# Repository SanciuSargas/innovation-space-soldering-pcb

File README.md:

# innovation-space-soldering-pcb
A beginner-friendly soldering practice PCB designed for workshops to teach fundamental soldering skills through a fun, hands-on project.

TODO: add soldering guide document

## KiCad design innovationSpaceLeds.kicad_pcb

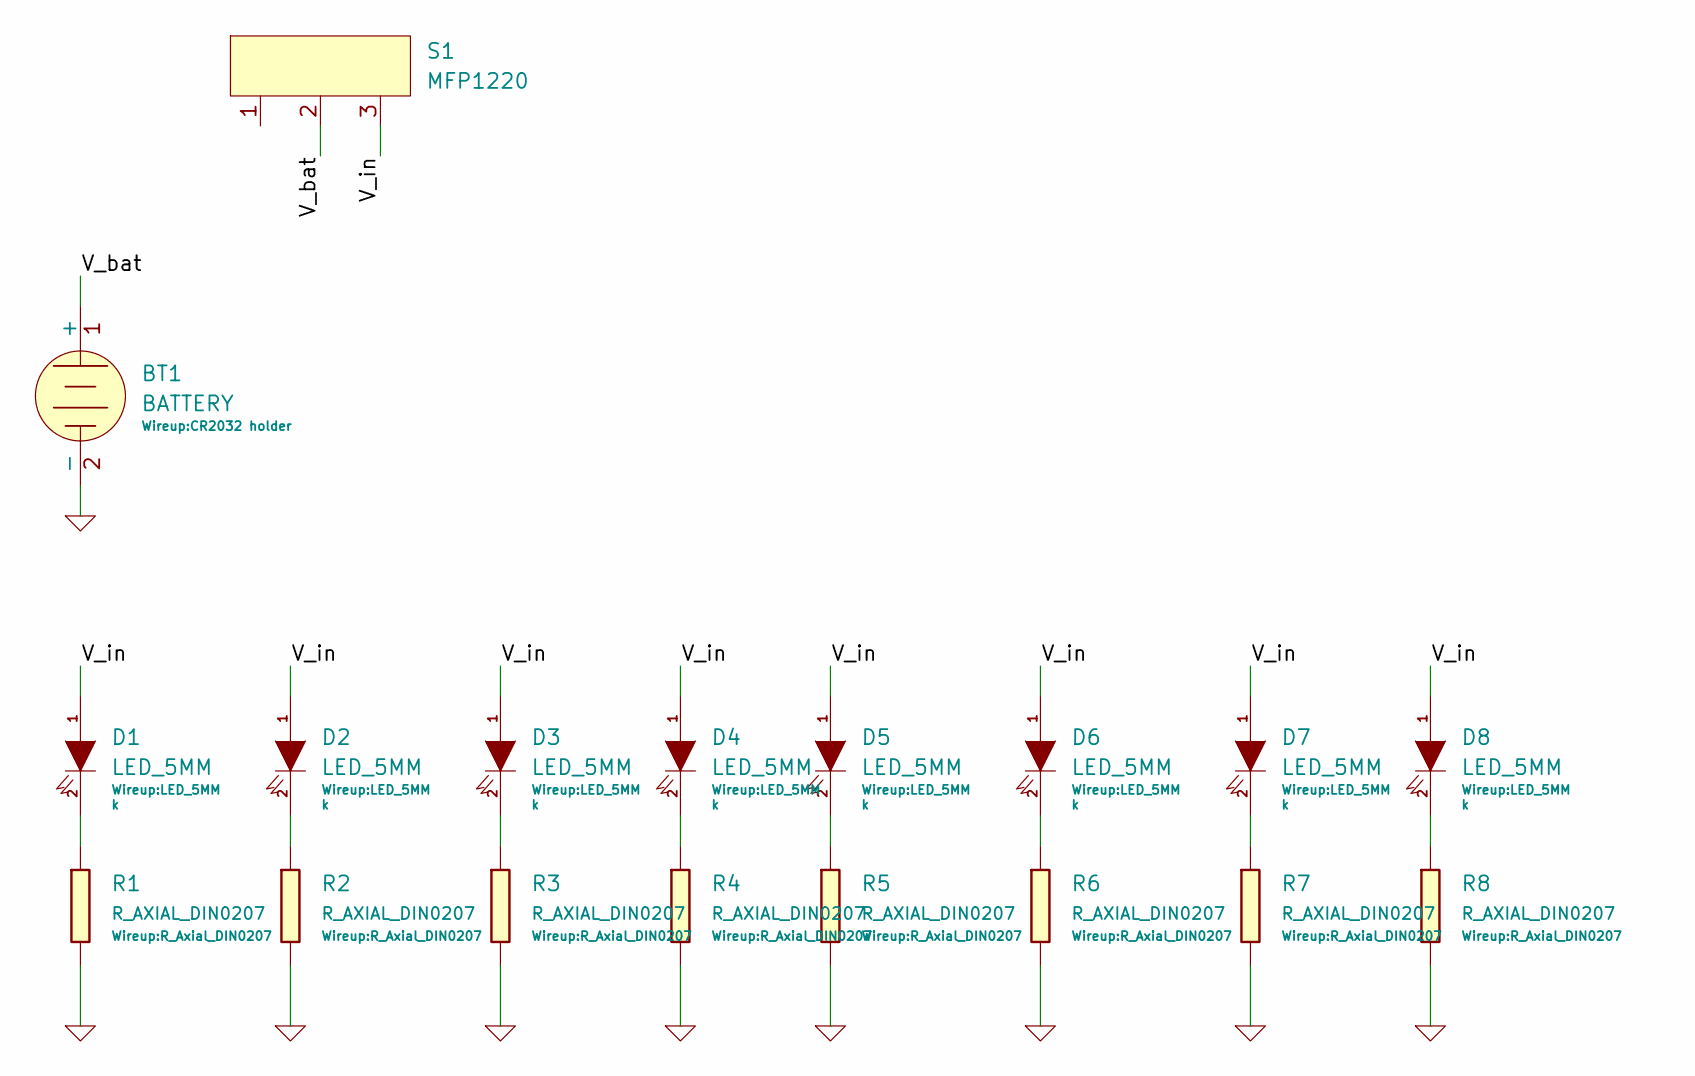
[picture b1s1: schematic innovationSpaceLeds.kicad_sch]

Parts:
BT1: BATTERY; CR2032 holder
D1, D2, D3, D4, D5, D6, D7, D8: LED_5MM
R1, R2, R3, R4, R5, R6, R7, R8: R_AXIAL_DIN0207; R_Axial_DIN0207
S1: MFP1220

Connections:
/V_bat: BT1.1 (+), S1.2
/V_in: D1.1 (A), D2.1 (A), D3.1 (A), D4.1 (A), D5.1 (A), D6.1 (A), D7.1 (A), D8.1 (A), S1.3
GND: BT1.2 (-), R1.2, R2.2, R3.2, R4.2, R5.2, R6.2, R7.2, R8.2
unnamed: D1.2 (K), R1.1
unnamed: D2.2 (K), R2.1
unnamed: D3.2 (K), R3.1
unnamed: D4.2 (K), R4.1
unnamed: D5.2 (K), R5.1
unnamed: D6.2 (K), R6.1
unnamed: D7.2 (K), R7.1
unnamed: D8.2 (K), R8.1

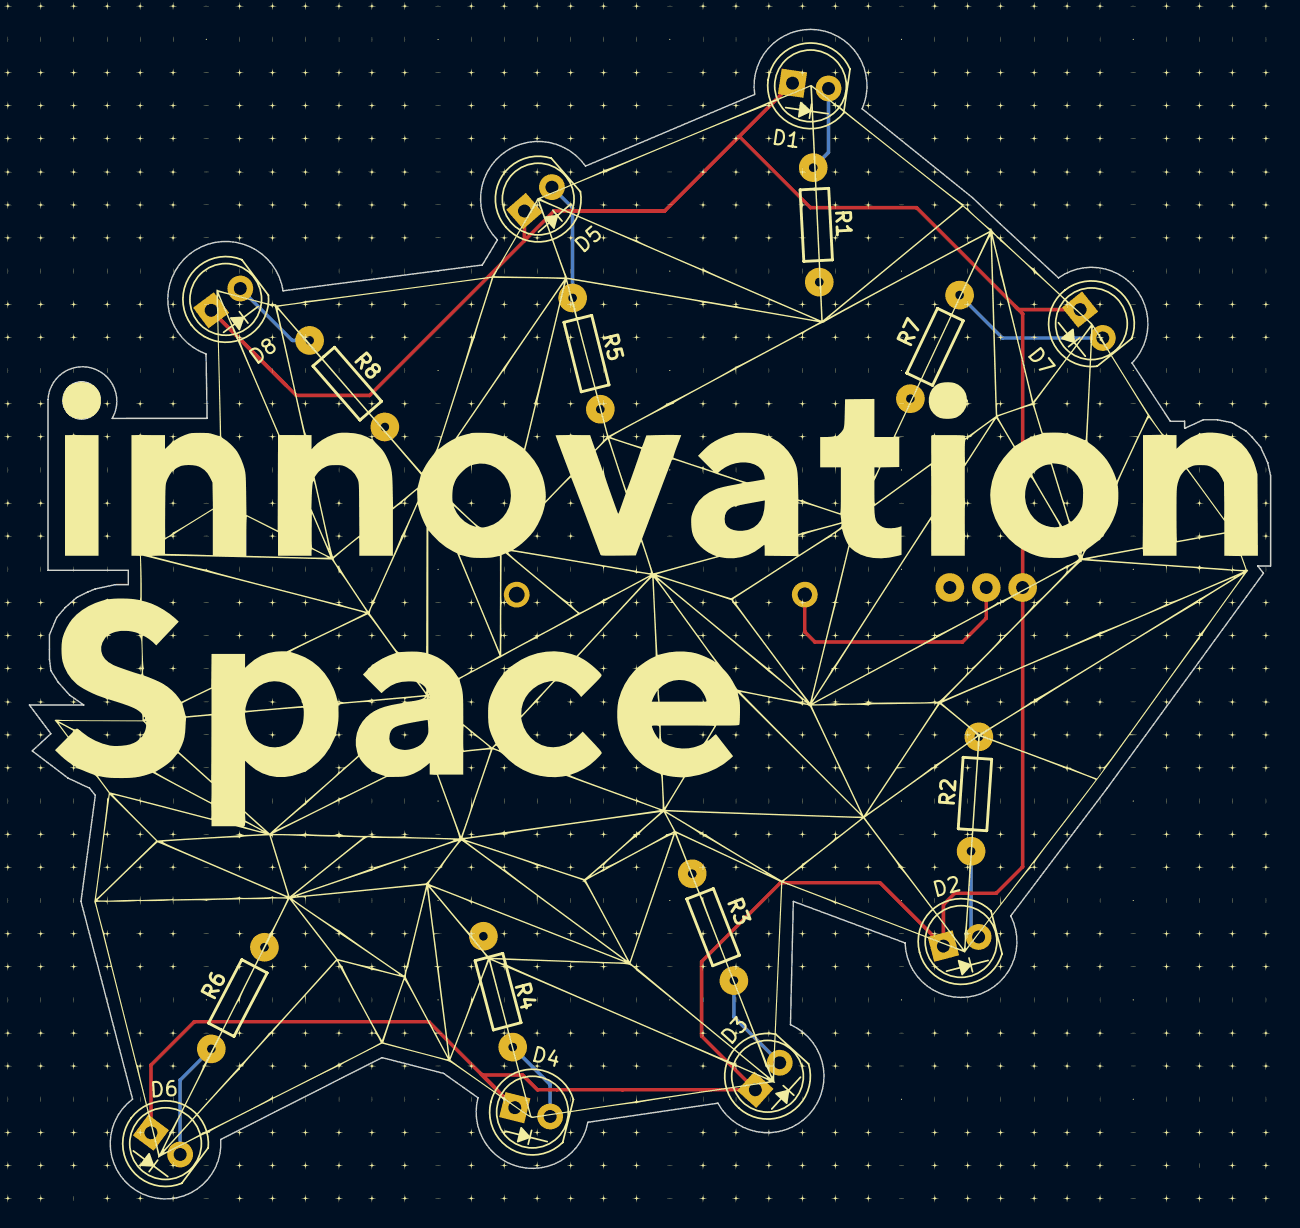
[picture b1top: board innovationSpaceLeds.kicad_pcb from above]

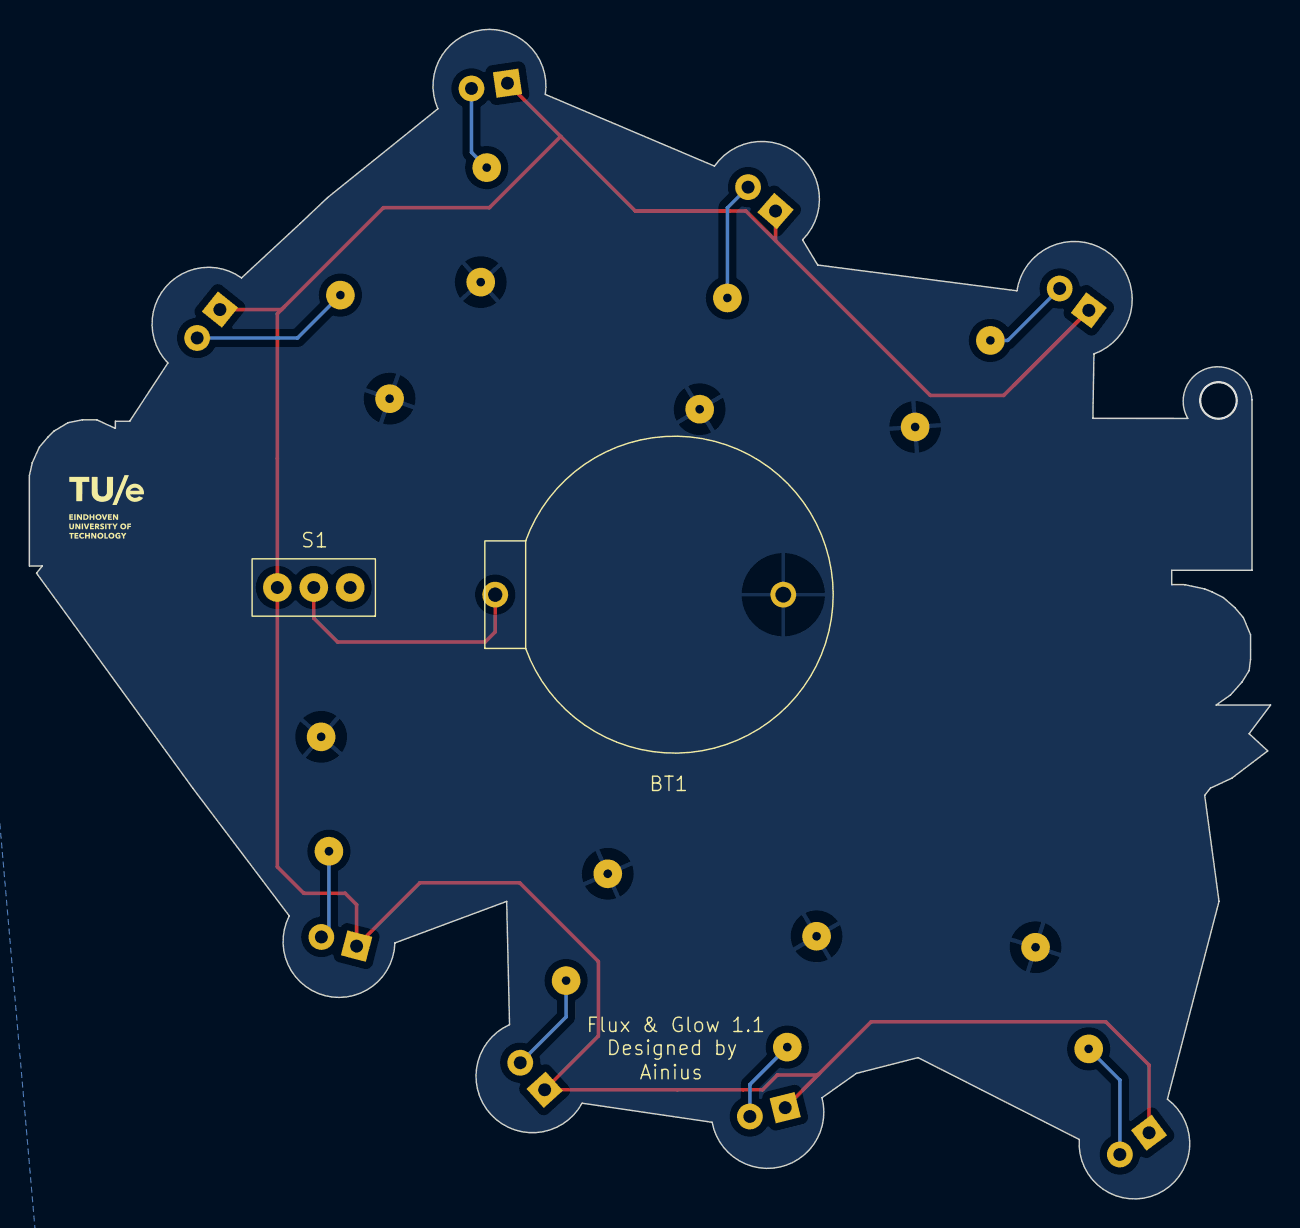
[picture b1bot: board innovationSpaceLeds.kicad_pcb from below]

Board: 2 copper layers, 86.6 x 81.6 mm, 18 parts (2 on the bottom side), 11 nets.

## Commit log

2025-09-04 add pcb files
